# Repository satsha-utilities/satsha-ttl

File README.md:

<div align="center"><h1 style="font-family: courier;" align="center">satsha-ttl</h1></div>

<div align="center"></div>
<div align="center"><i>An open source & fabbable USB to serial converter board.</i></div>

satsha-ttl
--

After some time of buying expensive FDTI cables (about 20$ nowadays) and having the need to use several USB to serial converters for my **[Fab Academy](http://fabacademy.org/)** students, I developed my own fabbable solution. satsha-ttl features a **[CH340G USB to serial chip](https://cdn.sparkfun.com/datasheets/Dev/Arduino/Other/CH340DS1.PDF)** and it is designed to be cheap, reliable and easy to be reproduced. It uses an LDO voltage regulator and a **jumper to switch between 3.3V and 5V**, both for power and logic levels of TX/RX. The design of the satsha-ttl also allows to easily integrate it into existing boards requiring an USB communication without having a dedicated hardware implemented into the microcontroller (eg the 328p).

Here are the **features of the satsha-ttl:**

- **CH340G** USB to serial chip
- selectable voltage of **3.3V and 5V** (both for power and serial)
- **250mA** current on 3.3V
- **USB power** for 5V
- **CTS and DTR** pins
- **mini USB** connector
- **no drivers** needed for latest Windows/MacOS/Linux
- size of **45x28mm**
- cost **1.3€/1.6$** (buying the components from China, **[BOM](https://gitlab.fabcloud.org/satsha/satsha-ttl/raw/master/docs/satsha-ttl-BOM.xlsx)**)

satsha-ttl **PCB**:

satsha-ttl **schematic**:

satsha-ttl **board**:

Downloads
--

**downloads (right click download as):**

- **[satsha-ttl schematic](https://github.com/satsha-utilities/satsha-ttl/raw/master/eagle/satsha-ttl/satsha-ttl.sch)**
- **[satsha-ttl board](https://github.com/satsha-utilities/satsha-ttl/raw/master/eagle/satsha-ttl/satsha-ttl.brd)**
- **[satsha-ttl internal traces png 0.1mm](https://github.com/satsha-utilities/satsha-ttl/raw/master/media/internal.png)**
- **[satsha-ttl cutout png 0.1mm](https://github.com/satsha-utilities/satsha-ttl/raw/master/media/cut.png)**
- **[satsha-ttl internal traces png 0.2mm](https://github.com/satsha-utilities/satsha-ttl/raw/master/media/internal_02.png)**
- **[satsha-ttl cutout png 0.2mm](https://github.com/satsha-utilities/satsha-ttl/raw/master/media/cut_02.png)**
- **[satsha-ttl BOM ods](https://github.com/satsha-utilities/satsha-ttl/raw/master/docs/satsha-ttl-BOM.ods)**
- **[satsha-ttl BOM xlsx](https://github.com/satsha-utilities/satsha-ttl/raw/master/docs/satsha-ttl-BOM.xlsx)**

Getting started with satsha-ttl
--
Before connecting satsha-ttl to your computer is really important to **check if the connections are ok**, as it could damage the USB port of our computer if they are wrong. A smoke test can also be done beforehand with an **USB hub or an USB power supply**.  Install the **drivers** for the CH340G if satsha-ttl is not recognized automatically from your OS. In case you are using Windows 8 or older, or older versions of MacOS/Linux download and install the **[drivers from here](https://sparks.gogo.co.nz/ch340.html)**. 

 Find below the **satsha-ttl pinout**:

satsha-ttl can be used to **supply power** to another microcontroller board, other than connecting the serial. In case of supplying power to another board make sure its voltage and current requirements matches the **selected voltage** on the satsha-ttl jumper and the **maximum current** the satsha-ttl/USB port can output. It is possible to use the satsha-ttl as a **programmer for AVR** microcontrollers with installed the Arduino bootloader, in this case the **DTR** is used **software reset** pin.

Here is an example scheme on how to connect **satsha-ttl to program a satshakit:**

Media
--

satsha-ttl pictures:

satsha-ttl connected with a satshakit:

satsha-ttl 1 million lines gcode test:

satsha-ttl 2 uploading to a satshakit using serial 5V:

satsha-ttl receiving data from software serial 3.3V:

satsha-ttl streaming gcode to grbl satshakit @250000 bauds 5V:

Author
--

- Daniele Ingrassia

Contact
--
- **ingrassiada@gmail.com**
- **[linkedin](http://it.linkedin.com/in/danieleingrassia)**

Thanks
--
[Fablab Kamp-Lintfort](http://fablab.hochschule-rhein-waal.de/index.php/de/)<br />
Hochschule Rhein-Waal<br />
Friedrich-Heinrich-Allee 25, 47475 Kamp-Lintfort, Germany<br />
fablab@hochschule-rhein-waal.de

License
--
This work is licensed under the terms of the open source license: Creative Commons Attribution-ShareAlike 4.0 International ([CC BY-SA 4.0](https://creativecommons.org/licenses/by-sa/4.0/)).

Disclaimer  
--

<div class="align-justify">
This hardware/software is provided "as is", and you use the hardware/software at your own risk. Under no circumstances shall any author be liable for direct, indirect, special, incidental, or consequential damages resulting from the use, misuse, or inability to use this hardware/software, even if the authors have been advised of the possibility of such damages.</div>

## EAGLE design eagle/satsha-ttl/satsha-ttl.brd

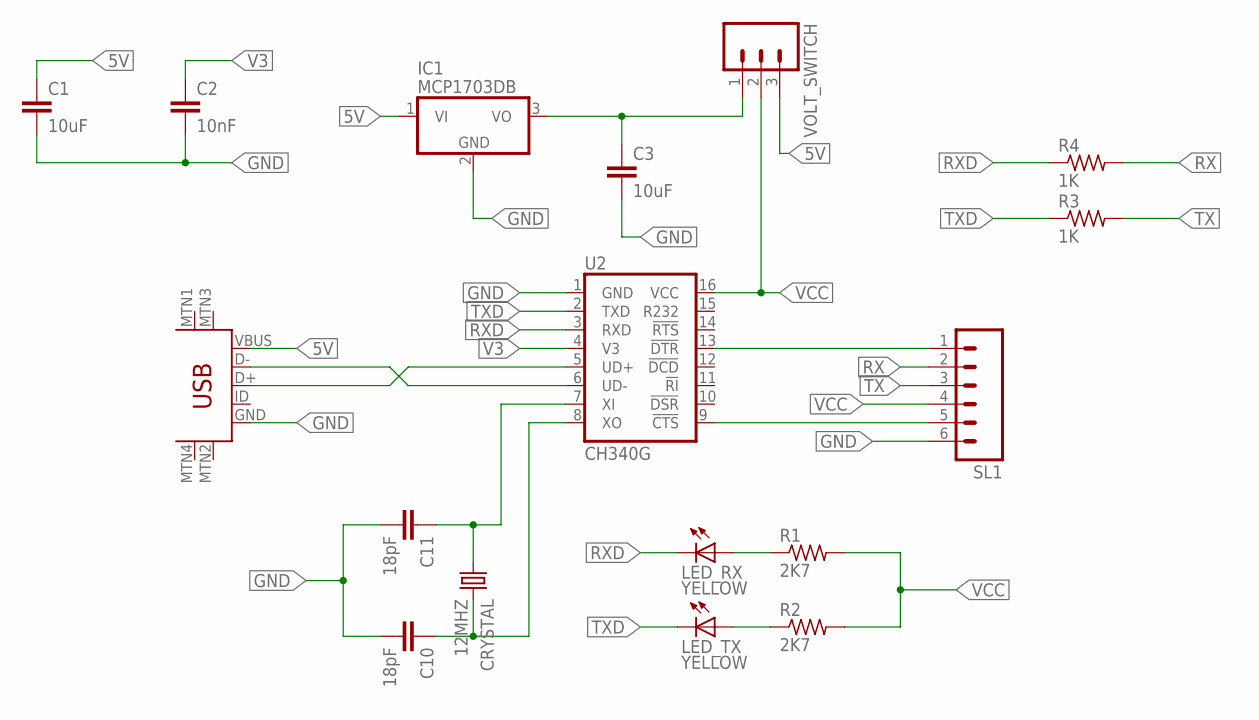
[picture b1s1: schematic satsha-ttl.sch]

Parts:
C1, C3: 10uF; 1206
C2: 10nF; 1206
C10, C11: 18pF; 1206
CRYSTAL: 12MHZ; CSM-7X-DU
IC1: MCP1703DB; SOT223
LED_RX: YELLOW; LED1206
LED_TX: YELLOW; LED1206
R1, R2: 2K7; R1206
R3, R4: 1K; R1206
SL1: M06; 06P
U2: CH340G; SO016
U$7: USB-MINIB-5PIN; USB-MINIB
VOLT_SWITCH: M03; 03P

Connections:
3V3: C3.1, IC1.3 (VO), VOLT_SWITCH.1
5V: C1.1, IC1.1 (VI), U$7.VBUS, VOLT_SWITCH.3
CTS: SL1.5, U2.9 (!CTS)
D+: U2.5 (UD+), U$7.D+
D-: U2.6 (UD-), U$7.D-
DTR: SL1.1, U2.13 (!DTR)
GND: C1.2, C2.2, C3.2, C10.2, C11.2, IC1.2 (GND), SL1.6, U2.1 (GND), U$7.GND
unnamed: LED_RX.1 (A), R1.1
unnamed: LED_TX.1 (A), R2.1
OSC_IN: C10.1, CRYSTAL.2, U2.8 (XO)
OSC_OUT: C11.1, CRYSTAL.1, U2.7 (XI)
RX: R4.2, SL1.2
RXD: LED_RX.2 (C), R4.1, U2.3 (RXD)
TX: R3.2, SL1.3
TXD: LED_TX.2 (C), R3.1, U2.2 (TXD)
V3: C2.1, U2.4 (V3)
VCC: R1.2, R2.2, SL1.4, U2.16 (VCC), VOLT_SWITCH.2

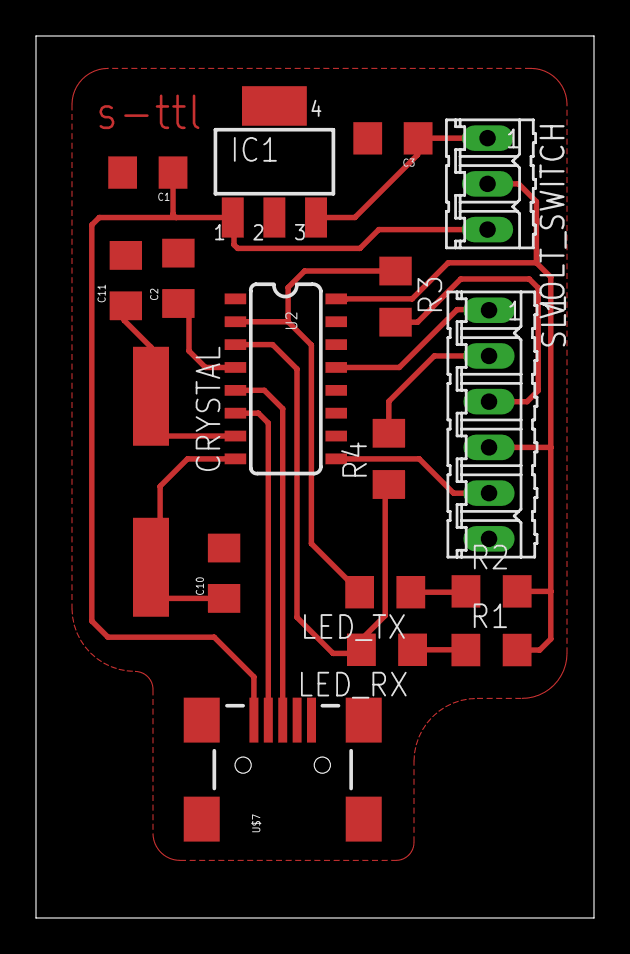
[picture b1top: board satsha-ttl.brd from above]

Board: 2 copper layers, 31.0 x 49.0 mm, 17 parts (0 on the bottom side), 17 nets.

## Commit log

2018-02-14 first commit imported from Fab Academy gitlab
2018-02-14 made link consistent with this repo
2018-02-18 added pngs for 0.2mm
2020-05-31 license change

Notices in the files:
parts and their libraries:
01_SparkFun: Licensing: CC v3.0 Share-Alike You are welcome to use this library for commercial purposes.
SparkFun-DigitalIC: Licensing: Creative Commons ShareAlike 4.0 International - https://creativecommons.org/licenses/by-sa/4.0
